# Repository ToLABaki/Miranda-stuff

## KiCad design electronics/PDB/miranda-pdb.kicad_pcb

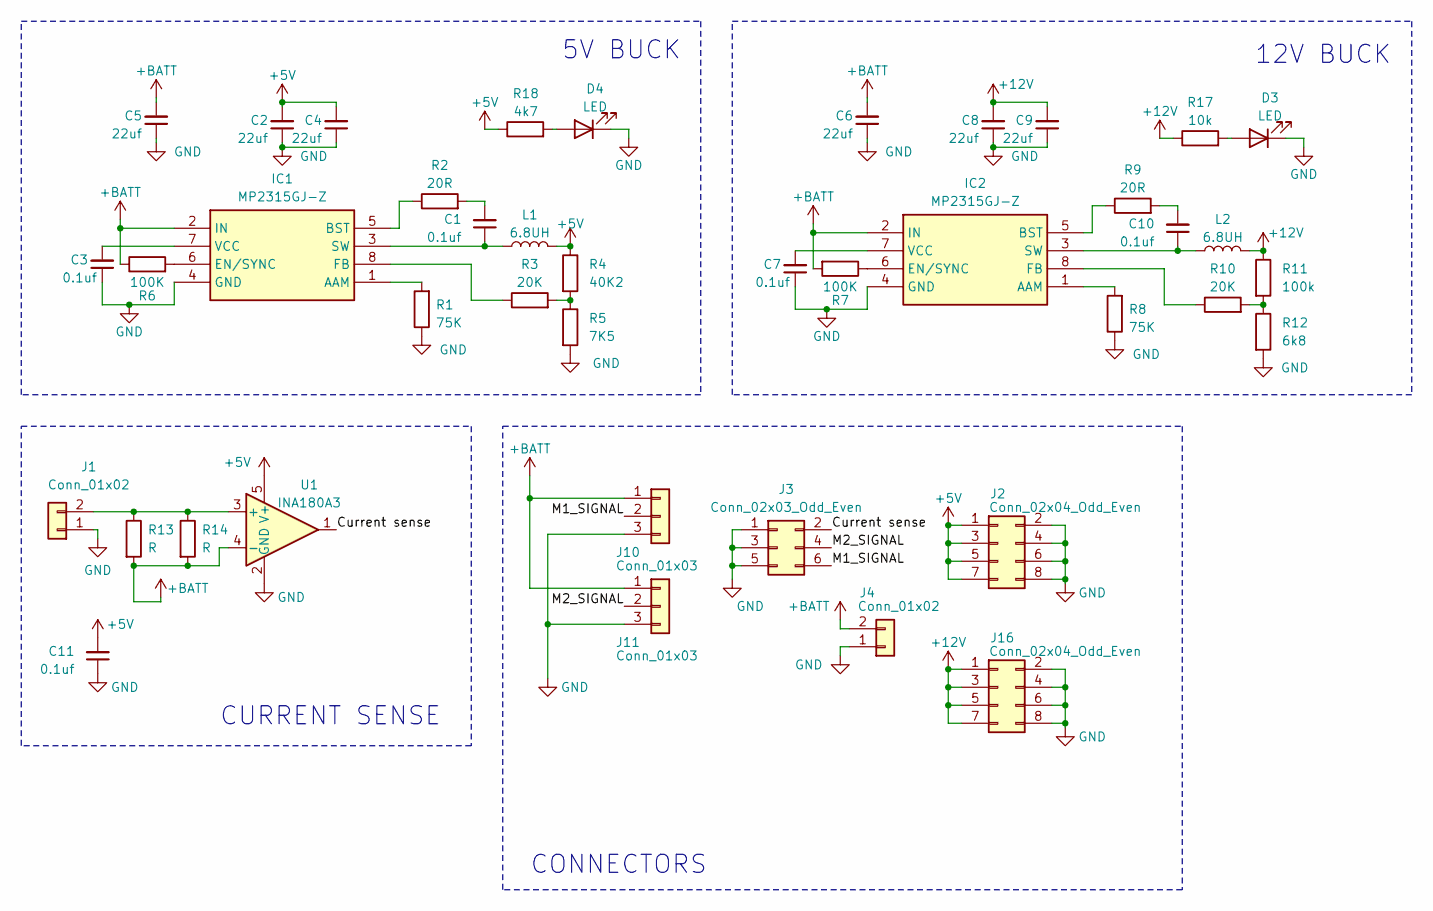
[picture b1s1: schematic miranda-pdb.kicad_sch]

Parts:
C1, C3, C7, C10, C11: 0.1uf; C_0805_2012Metric
C2, C4, C5, C6, C8, C9: 22uf; C_0805_2012Metric
D3, D4: LED; LED_0805_2012Metric_Pad1.15x1.40mm_HandSolder
IC1, IC2: MP2315GJ-Z; SOT65P280X100-8N; Manufacturer_Part_Number MP2315GJ-Z
J1, J4: Conn_01x02; solder pad
J2, J16: Conn_02x04_Odd_Even; PinHeader_2x04_P2.54mm_Horizontal
J3: Conn_02x03_Odd_Even; PinHeader_2x03_P2.54mm_Horizontal
J10, J11: Conn_01x03; MR30PW-FB
L1, L2: 6.8UH; L_Ferrocore_DLG-0703
R1, R8: 75K; R_0805_2012Metric_Pad1.20x1.40mm_HandSolder
R2, R9: 20R; R_0805_2012Metric_Pad1.20x1.40mm_HandSolder
R3, R10: 20K; R_0805_2012Metric_Pad1.20x1.40mm_HandSolder
R4: 40K2; R_0805_2012Metric_Pad1.20x1.40mm_HandSolder
R5: 7K5; R_0805_2012Metric_Pad1.20x1.40mm_HandSolder
R6, R7: 100K; R_0805_2012Metric_Pad1.20x1.40mm_HandSolder
R11: 100k; R_0805_2012Metric_Pad1.20x1.40mm_HandSolder
R12: 6k8; R_0805_2012Metric_Pad1.20x1.40mm_HandSolder
R13, R14: R; R_2512_6332Metric_Pad1.40x3.35mm_HandSolder
R17: 10k; R_0805_2012Metric_Pad1.20x1.40mm_HandSolder
R18: 4k7; R_0805_2012Metric_Pad1.20x1.40mm_HandSolder
U1: INA180A3; SOT-23-5

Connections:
+5V: C2.2, C4.2, C11.2, J2.1, J2.3, J2.5, J2.7, L1.2, R4.1, R18.1, U1.5 (V+)
+12V: C8.2, C9.2, J16.1, J16.3, J16.5, J16.7, L2.2, R11.1, R17.1
+BATT: C5.2, C6.2, IC1.2 (IN), IC2.2 (IN), J4.2, J10.1, J11.1, R6.1, R7.2, R13.2, R14.2, U1.4 (-)
/Current sense: J3.2, U1.1
/M1_SIGNAL: J3.6, J10.2
/M2_SIGNAL: J3.4, J11.2
GND: C2.1, C3.1, C4.1, C5.1, C6.1, C7.1, C8.1, C9.1, C11.1, D3.1 (K), D4.1 (K), IC1.4 (GND), IC2.4 (GND), J1.1, J2.2, J2.4, J2.6, J2.8, J3.1, J3.3, J3.5, J4.1, J10.3, J11.3, J16.2, J16.4, J16.6, J16.8, R1.1, R5.2, R8.1, R12.2, U1.2 (GND)
unnamed: C1.2, R2.2
unnamed: C10.2, R9.2
unnamed: D3.2 (A), R17.2
unnamed: D4.2 (A), R18.2
unnamed: IC1.1 (AAM), R1.2
unnamed: IC1.5 (BST), R2.1
unnamed: IC1.6 (EN/SYNC), R6.2
unnamed: IC1.8 (FB), R3.1
unnamed: C1.1, IC1.3 (SW), L1.1
unnamed: C3.2, IC1.7 (VCC)
unnamed: IC2.1 (AAM), R8.2
unnamed: IC2.5 (BST), R9.1
unnamed: IC2.6 (EN/SYNC), R7.1
unnamed: IC2.8 (FB), R10.1
unnamed: C10.1, IC2.3 (SW), L2.1
unnamed: C7.2, IC2.7 (VCC)
unnamed: J1.2, R13.1, R14.1, U1.3 (+)
unnamed: R3.2, R4.2, R5.1
unnamed: R10.2, R11.2, R12.1

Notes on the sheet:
5V BUCK
CONNECTORS
12V BUCK
CURRENT SENSE

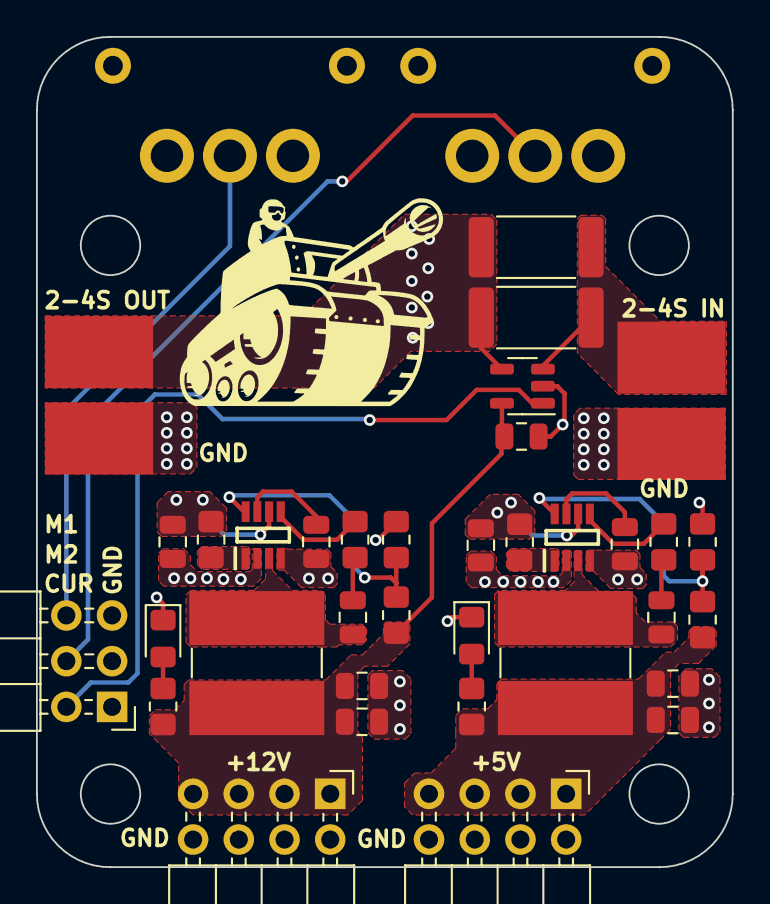
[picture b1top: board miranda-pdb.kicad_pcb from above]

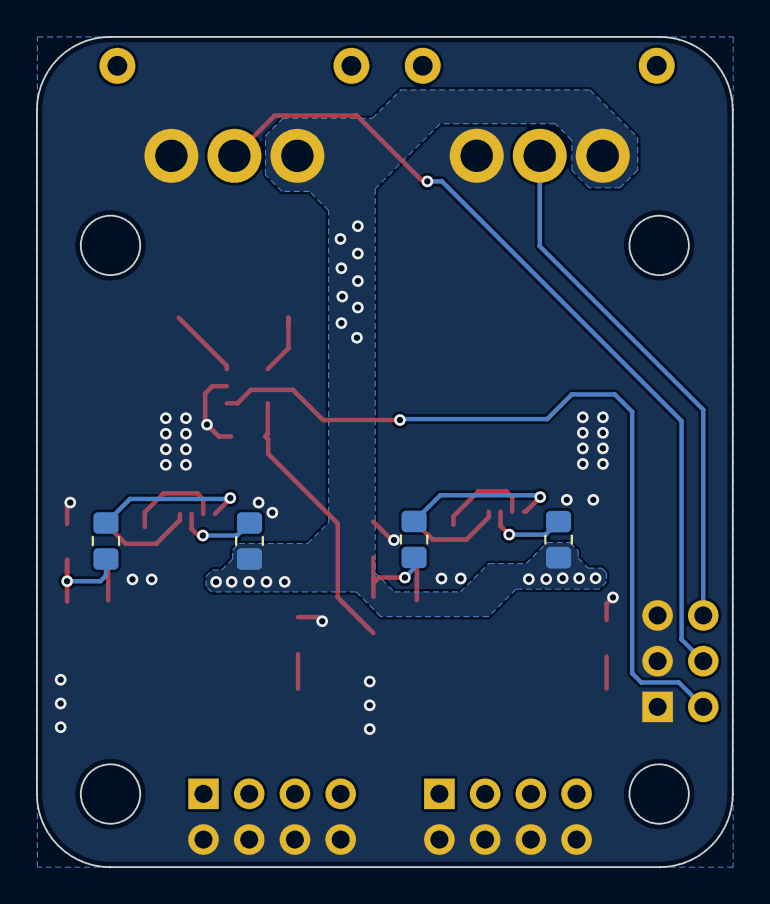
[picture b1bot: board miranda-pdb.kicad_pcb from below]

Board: 2 copper layers, 38.7 x 46.1 mm, 41 parts (4 on the bottom side), 26 nets.

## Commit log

2023-08-05 initial push
2023-08-30 finished pdb
